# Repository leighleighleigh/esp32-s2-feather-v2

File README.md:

# leighs-featherwings
Various feathers and featherwings of my own design. 
This repo currently in a state of disarray and abandonment.

I designed an [Adafruit Feather](https://learn.adafruit.com/adafruit-feather/feather-specification) form factor board based around an ESP32-S2 microcontroller module, driven out of the need for a suitable devboard for some of my projects. 

Featherwings for power+CAN, bluetooth audio, and I2S audio output, were also designed to accompany the ESP32-S2 feather. These were all intended to be used together, in various car-related projects.

The BM83 bluetooth audio featherwing was successful when used with a [UDA1334 DAC](https://learn.adafruit.com/adafruit-i2s-stereo-decoder-uda1334a), but it was incompatible with my own DAC featherwing due to I2S timing mis-configurations.

As many of these parts became unavailable in 2020 onward, development ceased. 
Going forward, lessons learnt from these PCBs will be applied to the [saab-93NG-bluetooth-aux](https://github.com/leighleighleigh/saab-93NG-bluetooth-aux) and [saab-93NG-HPD-hacker](https://github.com/leighleighleigh/saab-93NG-HPD-hacker) projects.

# Build Images

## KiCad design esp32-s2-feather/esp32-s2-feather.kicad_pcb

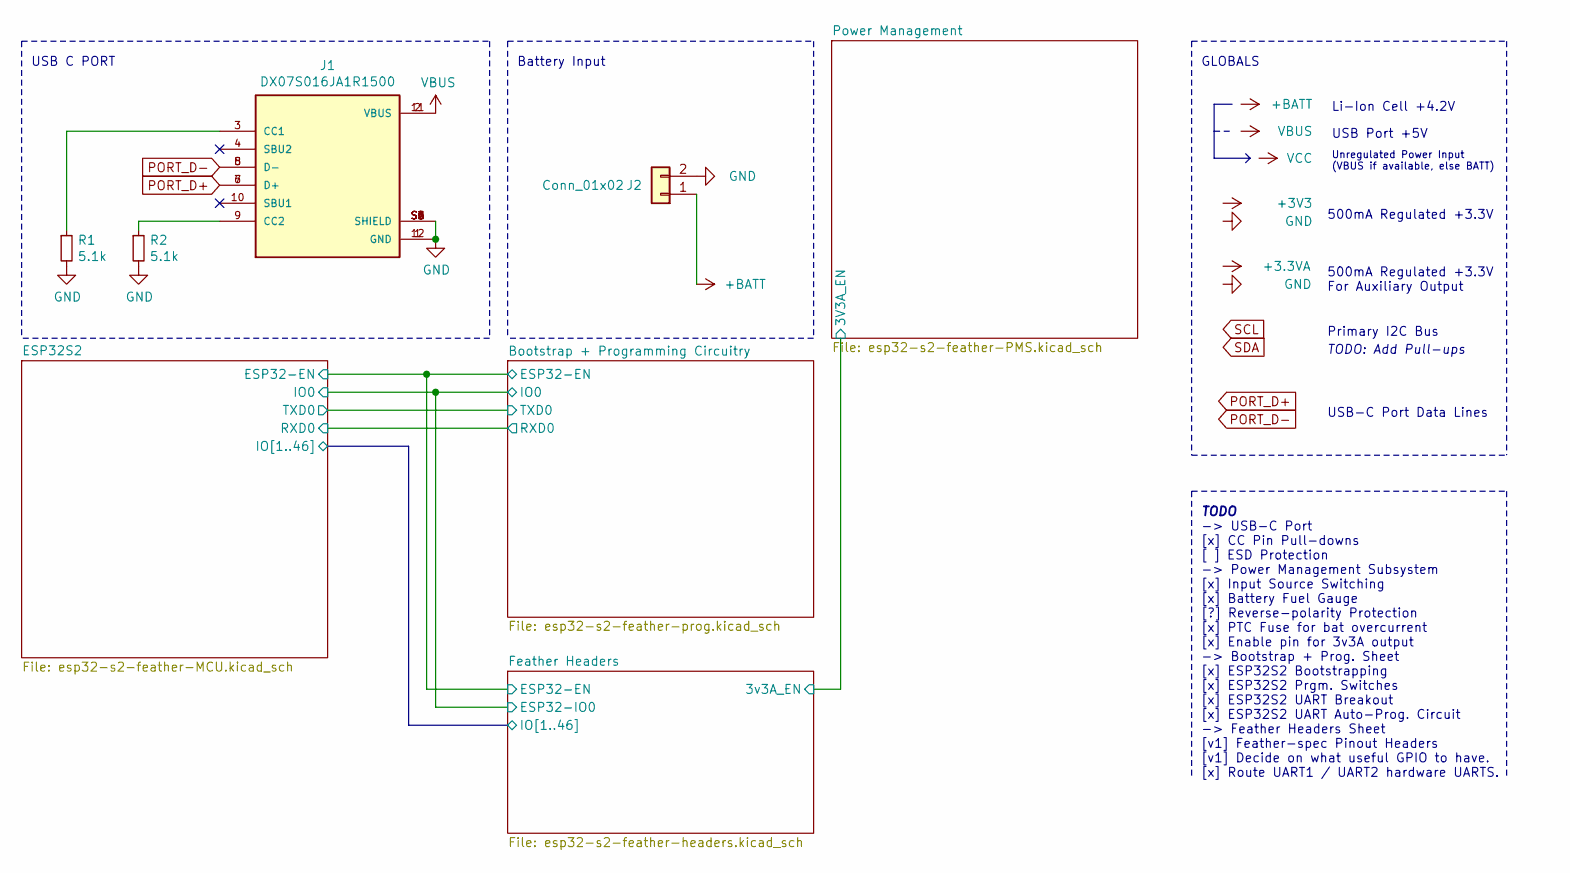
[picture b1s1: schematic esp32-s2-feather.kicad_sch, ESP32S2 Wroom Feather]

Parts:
J1: DX07S016JA1R1500; JAE_DX07S016JA1R1500; PARTREV 1
J2: Conn_01x02; JST_PH_S2B-PH-SM4-TB_1x02-1MP_P2.00mm_Horizontal
R1, R2: 5.1k; R_0805_2012Metric_Pad1.20x1.40mm_HandSolder

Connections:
+BATT: J2.1; also elsewhere on the board
GND: J1.1 (GND), J1.12 (GND), J1.S1 (SHIELD), J1.S2 (SHIELD), J1.S3 (SHIELD), J1.S4 (SHIELD), J1.S5 (SHIELD), J1.S6 (SHIELD), J2.2, R1.2, R2.2; also elsewhere on the board
unnamed: J1.3 (CC1), R1.1
unnamed: J1.9 (CC2), R2.1
PORT_D+: J1.6 (D+), J1.7 (D+); also elsewhere on the board
PORT_D-: J1.5 (D-), J1.8 (D-); also elsewhere on the board
VBUS: J1.2 (VBUS), J1.11 (VBUS); also elsewhere on the board

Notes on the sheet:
USB C PORT
Battery Input
GLOBALS
TODO
-> USB-C Port [x] CC Pin Pull-downs [ ] ESD Protection -> Power Management Subsystem [x] Input Source Switching [x] Battery Fuel Gauge [?] Reverse-polarity Protection [x] PTC Fuse for bat overcurrent [x] Enable pin for 3v3A output -> Bootstrap + Prog. Sheet [x] ESP32S2 Bootstrapping [x] ESP32S2 Prg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
500mA Regulated +3.3V
500mA Regulated +3.3V For Auxiliary Output
Primary I2C Bus
TODO: Add Pull-ups
USB-C Port Data Lines
Li-Ion Cell +4.2V
USB Port +5V
Unregulated Power Input (VBUS if available, else BATT)

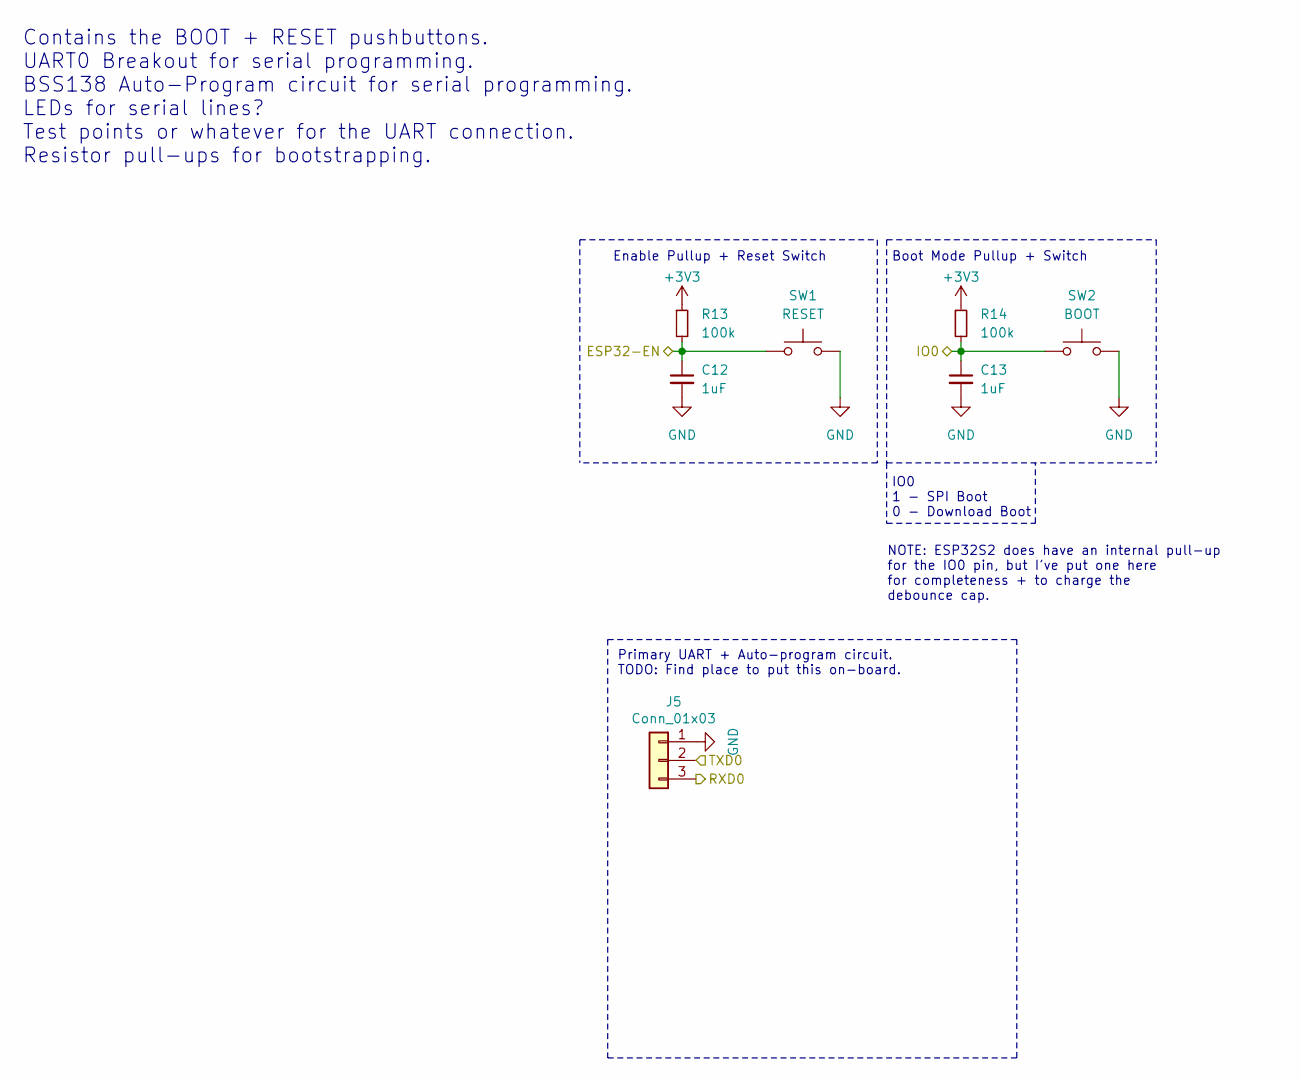
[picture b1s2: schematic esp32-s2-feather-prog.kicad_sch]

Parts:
C12, C13: 1uF; C_0805_2012Metric_Pad1.18x1.45mm_HandSolder
J5: Conn_01x03; SolderWirePad_1x03_P3.175mm_Drill0.8mm
R13, R14: 100k; R_0805_2012Metric_Pad1.20x1.40mm_HandSolder
SW1: RESET; PTS636SK25SMTRLFS
SW2: BOOT; PTS636SK25SMTRLFS

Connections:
+3V3: R13.1, R14.1; also elsewhere on the board
/ESP32-EN: C12.1, R13.2, SW1.1; also elsewhere on the board
/IO0: C13.1, R14.2, SW2.1; also elsewhere on the board
GND: C12.2, C13.2, J5.1, SW1.2, SW2.2; also elsewhere on the board

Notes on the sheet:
Contains the BOOT + RESET pushbuttons. UART0 Breakout for serial programming. BSS138 Auto-Program circuit for serial programming. LEDs for serial lines? Test points or whatever for the UART connection. Resistor pull-ups for bootstrapping.
Enable Pullup + Reset Switch
Primary UART + Auto-program circuit. TODO: Find place to put this on-board.
NOTE: ESP32S2 does have an internal pull-up for the IO0 pin, but I've put one here for completeness + to charge the debounce cap.
Boot Mode Pullup + Switch
IO0 1 - SPI Boot 0 - Download Boot

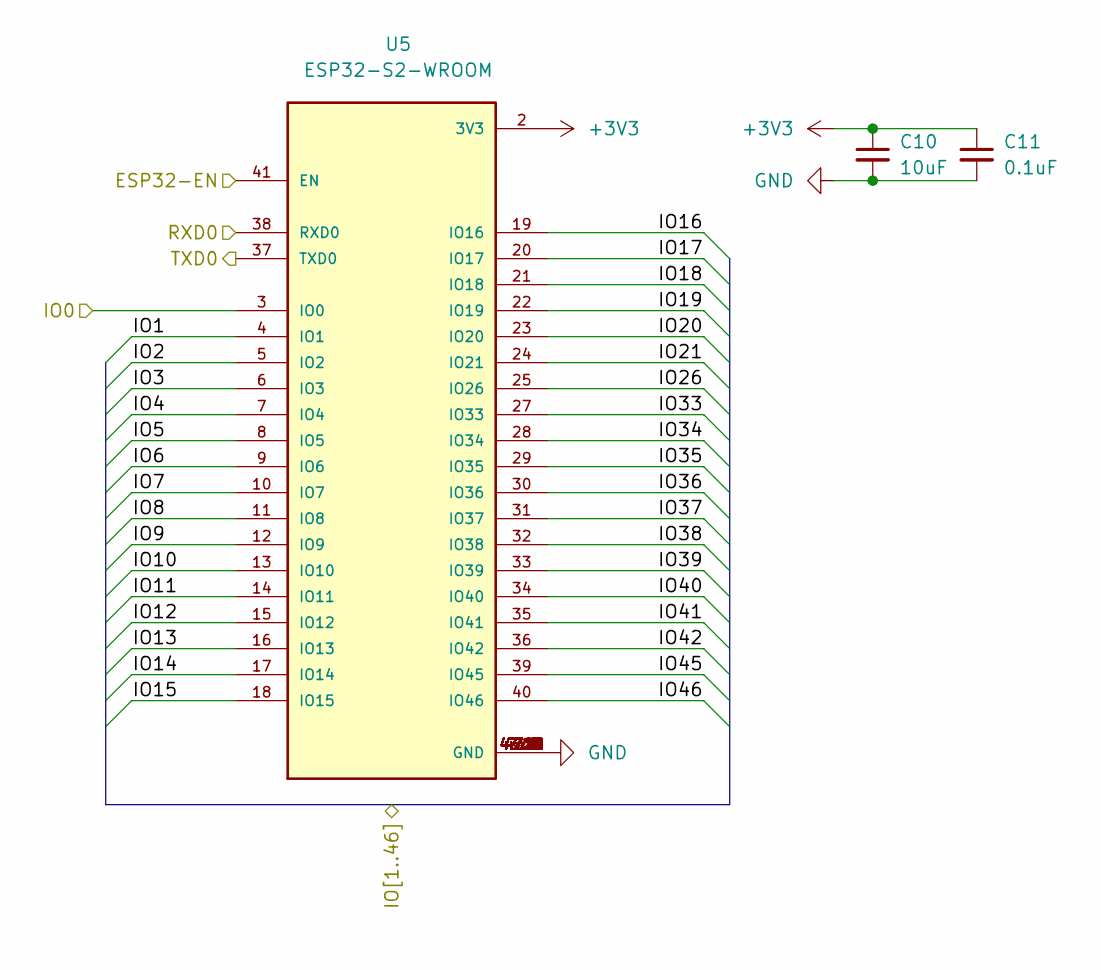
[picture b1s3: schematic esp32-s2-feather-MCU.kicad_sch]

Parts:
C10: 10uF; C_0805_2012Metric_Pad1.18x1.45mm_HandSolder
C11: 0.1uF; C_0805_2012Metric_Pad1.18x1.45mm_HandSolder
U5: ESP32-S2-WROOM; XCVR_ESP32-S2-WROOM-TinyPads; PARTREV V1.0

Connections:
+3V3: C10.1, C11.1, U5.2 (3V3); also elsewhere on the board
/ESP32-EN: U5.41 (EN); also elsewhere on the board
/IO0: U5.3 (IO0); also elsewhere on the board
/IO1: U5.4 (IO1); also elsewhere on the board
/IO2: U5.5 (IO2); also elsewhere on the board
/IO3: U5.6 (IO3); also elsewhere on the board
/IO4: U5.7 (IO4); also elsewhere on the board
/IO5: U5.8 (IO5); also elsewhere on the board
/IO6: U5.9 (IO6); also elsewhere on the board
/IO7: U5.10 (IO7); also elsewhere on the board
/IO10: U5.13 (IO10)
/IO11: U5.14 (IO11)
/IO12: U5.15 (IO12); also elsewhere on the board
/IO13: U5.16 (IO13)
/IO14: U5.17 (IO14); also elsewhere on the board
/IO15: U5.18 (IO15)
/IO16: U5.19 (IO16)
/IO17: U5.20 (IO17); also elsewhere on the board
/IO18: U5.21 (IO18); also elsewhere on the board
/IO21: U5.24 (IO21); also elsewhere on the board
/IO26: U5.25 (IO26); also elsewhere on the board
/IO33: U5.27 (IO33); also elsewhere on the board
/IO34: U5.28 (IO34); also elsewhere on the board
/IO35: U5.29 (IO35); also elsewhere on the board
/IO36: U5.30 (IO36); also elsewhere on the board
/IO37: U5.31 (IO37); also elsewhere on the board
/IO38: U5.32 (IO38)
/IO39: U5.33 (IO39)
/IO40: U5.34 (IO40)
/IO41: U5.35 (IO41)
/IO42: U5.36 (IO42)
/IO45: U5.39 (IO45)
/IO46: U5.40 (IO46)
/RXD0: U5.38 (RXD0); also elsewhere on the board
/TXD0: U5.37 (TXD0); also elsewhere on the board
GND: C10.2, C11.2, U5.1 (GND), U5.26 (GND), U5.42 (GND), U5.43.1 (GND), U5.43.2 (GND), U5.43.3 (GND), U5.43.4 (GND), U5.43.5 (GND), U5.43.6 (GND), U5.43.7 (GND), U5.43.8 (GND), U5.43.9 (GND), U5.43.10 (GND), U5.43.11 (GND), U5.43.12 (GND), U5.43.13 (GND), U5.43.14 (GND), U5.43.15 (GND), U5.43.16 (GND), U5.43.17 (GND), U5.43.18 (GND), U5.43.19 (GND), U5.43.20 (GND), U5.43.21 (GND); also elsewhere on the board
PORT_D+: U5.23 (IO20); also elsewhere on the board
PORT_D-: U5.22 (IO19); also elsewhere on the board
SCL: U5.12 (IO9); also elsewhere on the board
SDA: U5.11 (IO8); also elsewhere on the board

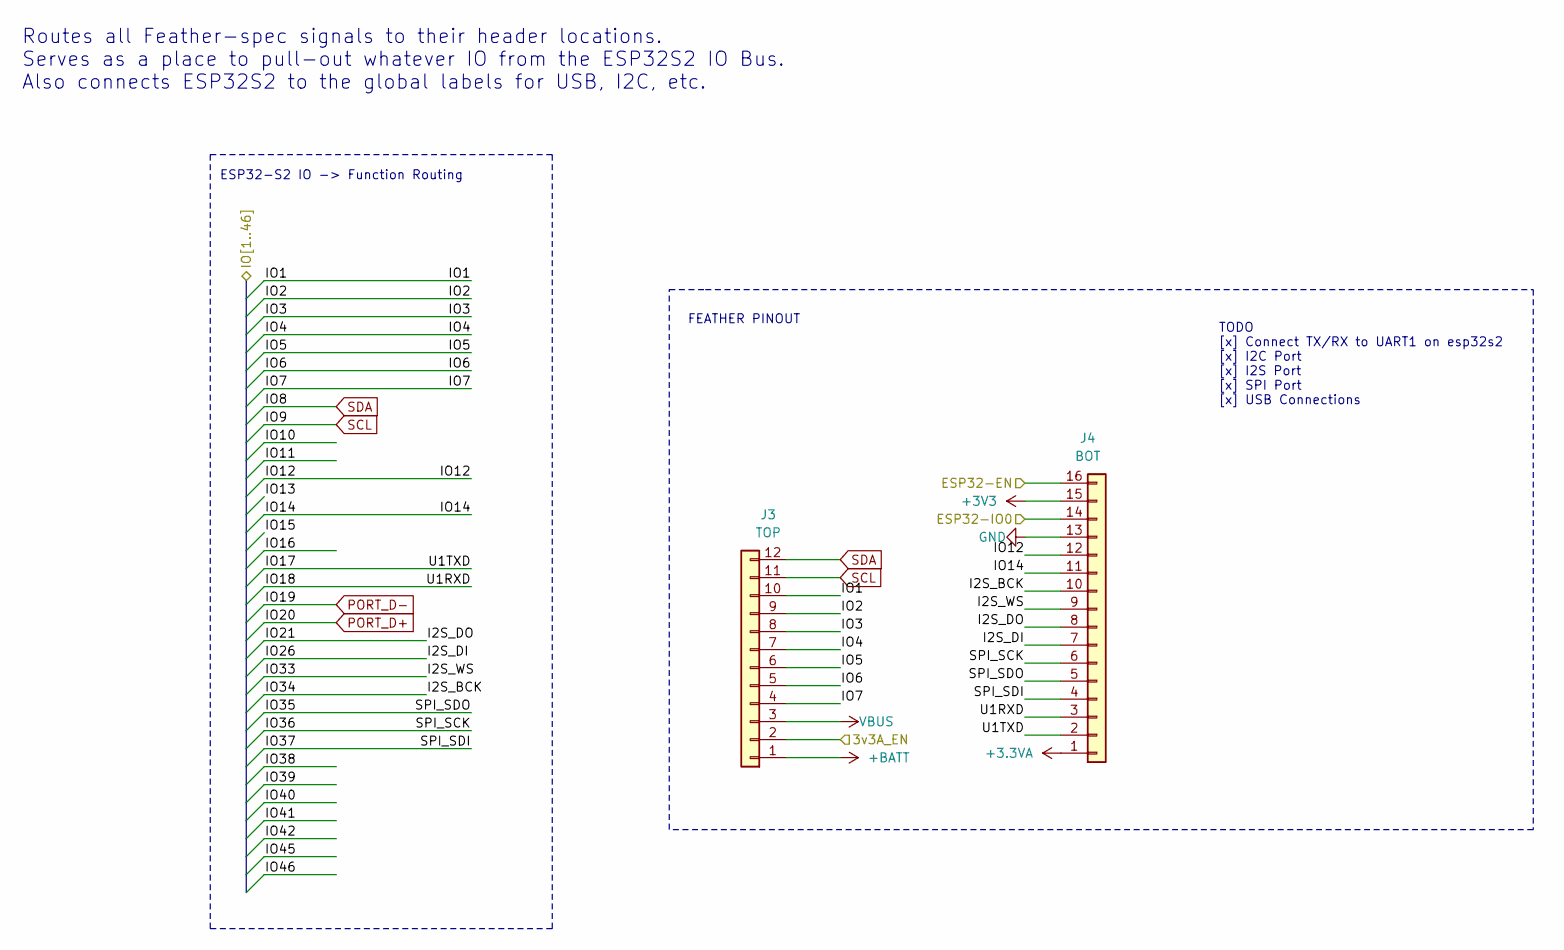
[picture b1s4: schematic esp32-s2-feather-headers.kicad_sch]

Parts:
J3: TOP; RoundPinHeader_1x12
J4: BOT; RoundPinHeader_1x16

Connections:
+3.3VA: J4.1; also elsewhere on the board
+3V3: J4.15; also elsewhere on the board
+BATT: J3.1; also elsewhere on the board
/3V3A_EN: J3.2; also elsewhere on the board
/ESP32-EN: J4.16; also elsewhere on the board
/IO0: J4.14; also elsewhere on the board
/IO1: J3.10; also elsewhere on the board
/IO2: J3.9; also elsewhere on the board
/IO3: J3.8; also elsewhere on the board
/IO4: J3.7; also elsewhere on the board
/IO5: J3.6; also elsewhere on the board
/IO6: J3.5; also elsewhere on the board
/IO7: J3.4; also elsewhere on the board
/IO12: J4.12; also elsewhere on the board
/IO14: J4.11; also elsewhere on the board
/IO17: J4.2; also elsewhere on the board
/IO18: J4.3; also elsewhere on the board
/IO21: J4.8; also elsewhere on the board
/IO26: J4.7; also elsewhere on the board
/IO33: J4.9; also elsewhere on the board
/IO34: J4.10; also elsewhere on the board
/IO35: J4.5; also elsewhere on the board
/IO36: J4.6; also elsewhere on the board
/IO37: J4.4; also elsewhere on the board
GND: J4.13; also elsewhere on the board
SCL: J3.11; also elsewhere on the board
SDA: J3.12; also elsewhere on the board
VBUS: J3.3; also elsewhere on the board

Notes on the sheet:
Routes all Feather-spec signals to their header locations. Serves as a place to pull-out whatever IO from the ESP32S2 IO Bus. Also connects ESP32S2 to the global labels for USB, I2C, etc.
ESP32-S2 IO -> Function Routing
FEATHER PINOUT
TODO [x] Connect TX/RX to UART1 on esp32s2 [x] I2C Port [x] I2S Port [x] SPI Port [x] USB Connections

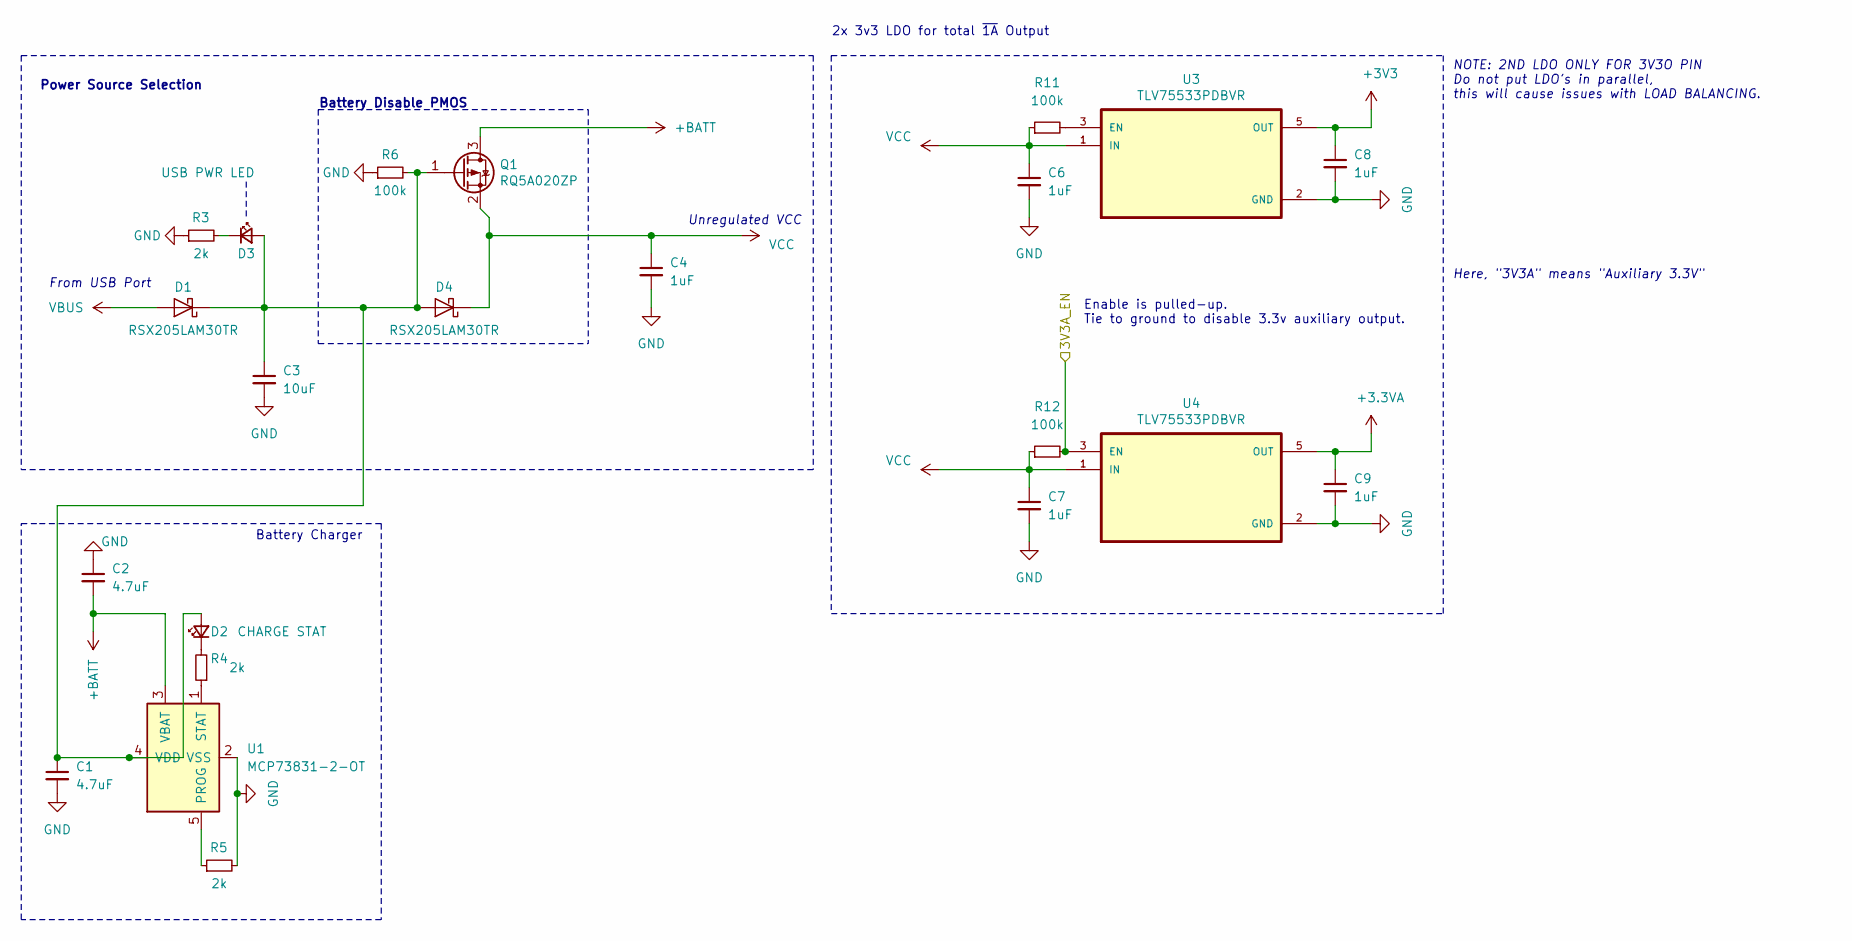
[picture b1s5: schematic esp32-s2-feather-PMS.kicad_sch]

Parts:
C1, C2: 4.7uF; C_0805_2012Metric_Pad1.18x1.45mm_HandSolder
C3: 10uF; C_0805_2012Metric_Pad1.18x1.45mm_HandSolder
C4, C6, C7, C8, C9: 1uF; C_0805_2012Metric_Pad1.18x1.45mm_HandSolder
D1, D4: RSX205LAM30TR; D_SOD-128
D2: CHARGE STAT; LED_0805_2012Metric_Pad1.15x1.40mm_HandSolder
D3: USB PWR LED; LED_0805_2012Metric_Pad1.15x1.40mm_HandSolder
Q1: RQ5A020ZP; SOT346
R3, R4, R5: 2k; R_0805_2012Metric_Pad1.20x1.40mm_HandSolder
R6, R11, R12: 100k; R_0805_2012Metric_Pad1.20x1.40mm_HandSolder
U1: MCP73831-2-OT; SOT-23-5
U3, U4: TLV75533PDBVR; SOT95P280X145-5N

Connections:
+3.3VA: C9.1, U4.5 (OUT); also elsewhere on the board
+3V3: C8.1, U3.5 (OUT); also elsewhere on the board
+BATT: C2.2, Q1.3 (D), U1.3 (VBAT); also elsewhere on the board
/3V3A_EN: R12.2, U4.3 (EN); also elsewhere on the board
GND: C1.2, C2.1, C3.2, C4.2, C6.2, C7.2, C8.2, C9.2, R3.1, R5.2, R6.1, U1.2 (VSS), U3.2 (GND), U4.2 (GND); also elsewhere on the board
unnamed: C1.1, C3.1, D1.1 (K), D2.2 (A), D3.2 (A), D4.2 (A), Q1.1 (G), R6.2, U1.4 (VDD)
unnamed: D2.1 (K), R4.2
unnamed: D3.1 (K), R3.2
unnamed: R4.1, U1.1 (STAT)
unnamed: R5.1, U1.5 (PROG)
unnamed: R11.2, U3.3 (EN)
VBUS: D1.2 (A); also elsewhere on the board
VCC: C4.1, C6.1, C7.1, D4.1 (K), Q1.2 (S), R11.1, R12.1, U3.1 (IN), U4.1 (IN)

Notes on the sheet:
Power Source Selection
From USB Port
Battery Disable PMOS
Battery Charger
Unregulated VCC
2x 3v3 LDO for total ~1A Output
Enable is pulled-up. Tie to ground to disable 3.3v auxiliary output.
NOTE: 2ND LDO ONLY FOR 3V3O PIN Do not put LDO's in parallel, this will cause issues with LOAD BALANCING.
Here, "3V3A" means "Auxiliary 3.3V"

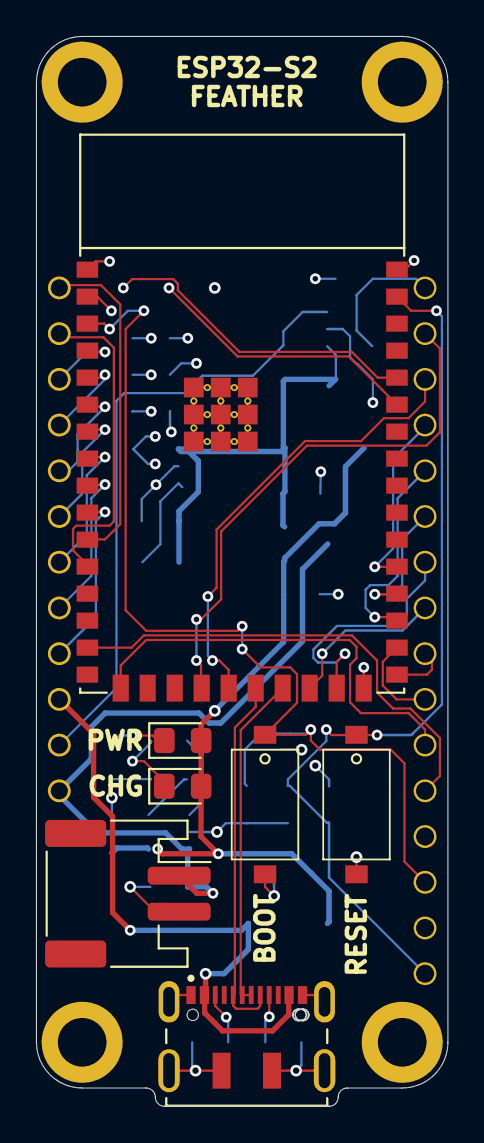
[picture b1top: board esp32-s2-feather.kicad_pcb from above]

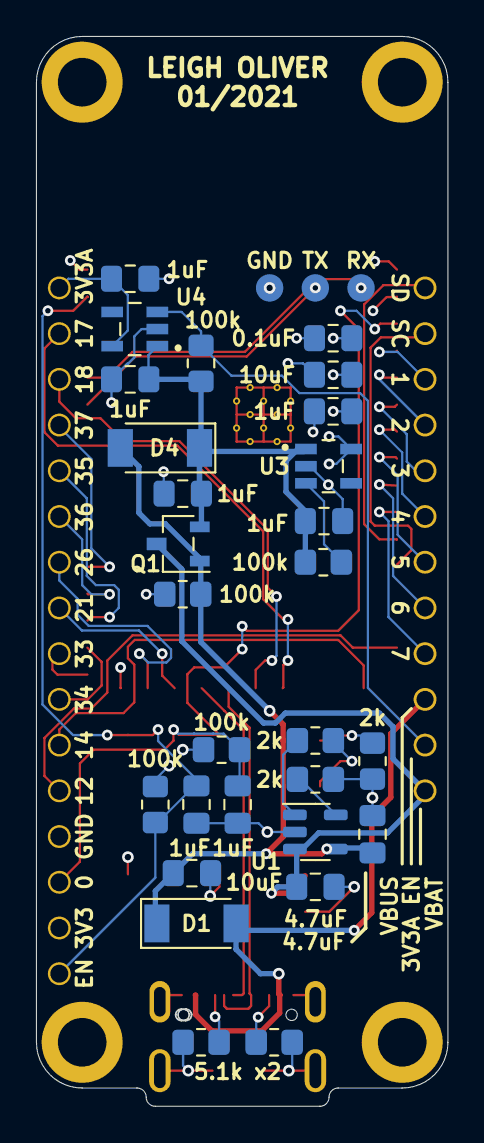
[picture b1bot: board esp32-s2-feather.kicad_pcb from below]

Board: 4 copper layers, 22.8 x 59.4 mm, 38 parts (29 on the bottom side), 41 nets.

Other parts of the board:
GND: Conn_01x03; SolderWirePad_1x03_P3.175mm_Drill0.8mm

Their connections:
/RXD0: GND.3; also elsewhere on the board
/TXD0: GND.2; also elsewhere on the board
GND: GND.1; also elsewhere on the board

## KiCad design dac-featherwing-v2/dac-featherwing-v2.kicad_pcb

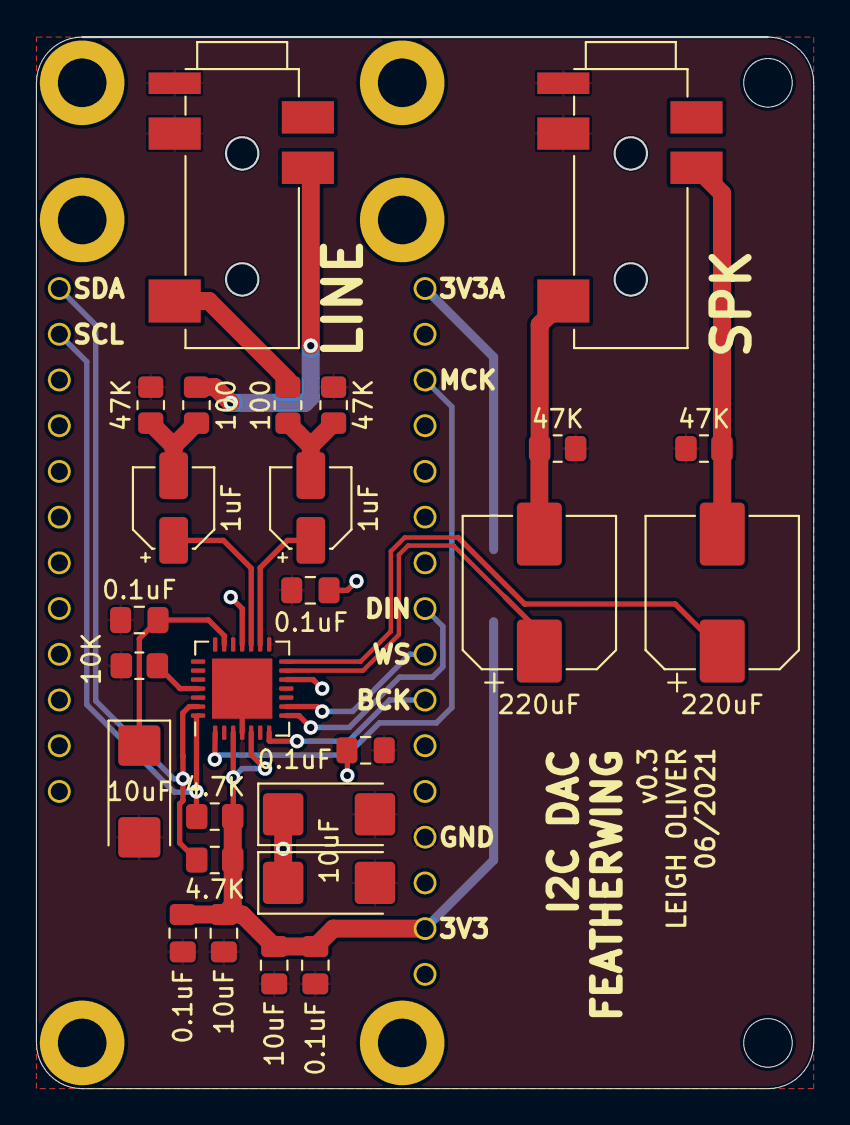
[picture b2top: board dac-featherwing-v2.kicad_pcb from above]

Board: 2 copper layers, 43.1 x 58.4 mm, 29 parts (1 on the bottom side), 22 nets.

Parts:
3V3A SRC: 3V3A SRC; SolderJumper-3_P2.0mm_Open_TrianglePad1.0x1.5mm_NumberLabels
C1, C4, C5, C8, C9: 0.1uF; C_0805_2012Metric_Pad1.18x1.45mm_HandSolder
C2, C3: 10uF; C_0805_2012Metric_Pad1.18x1.45mm_HandSolder
C6, C7, C14: 10uF; CP_EIA-6032-20_AVX-F_Pad2.25x2.35mm_HandSolder
C10, C12: 1uF; CP_Elec_4x4.5
C11, C13: 220uF; CP_Elec_8x10
J1: BOT; RoundPinHeader_1x16
J2: TOP; RoundPinHeader_1x12
J3: SPK; Lumberg 1503 20 VP3
J4: LINE; Lumberg 1503 20 VP3
R1, R2: 4.7K; R_0805_2012Metric_Pad1.20x1.40mm_HandSolder
R3: 10K; R_0805_2012Metric_Pad1.20x1.40mm_HandSolder
R5, R6, R7, R8: 47K; R_0805_2012Metric_Pad1.20x1.40mm_HandSolder
R9, R10: 100; R_0805_2012Metric_Pad1.20x1.40mm_HandSolder
U1: WM8731CLSEFL; QFN-28-1EP_5x5mm_P0.5mm_EP3.35x3.35mm

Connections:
+3.3VA: 3V3A SRC.2 (C), C5.1, C6.1, C7.1, C8.1, U1.12 (HPVDD), U1.18 (AVDD)
+3.3VDAC: 3V3A SRC.3 (B), J1.1
+3V3: 3V3A SRC.1 (A), C1.1, C2.1, C3.1, C4.1, J1.15, R1.1, R2.2, U1.3 (DCVDD), U1.5 (DBVDD)
/I2S_BCK: J1.10, U1.7 (BCLK)
/I2S_DO: J1.8, U1.8 (DACDAT)
/I2S_MCLK: J1.3, U1.1 (XTI/MCLK)
/I2S_WS: J1.9, U1.9 (DACLRC)
GND: C1.2, C2.2, C3.2, C4.2, C5.2, C6.2, C7.2, C8.2, C9.2, C14.2, J1.13, J3.R2, J3.S, J4.R2, J4.S, R3.2, R5.1, R6.2, R7.1, R8.2, U1.4 (DGND), U1.15 (HPGND), U1.19 (AGND), U1.26 (~CSB), U1.29 (AGND)
LHPOUT: C11.2, J3.T, R5.2
LOUT: J4.T, R10.2
unnamed: C10.1, U1.17 (ROUT)
unnamed: C10.2, R7.2, R9.1
unnamed: C11.1, U1.13 (LHPOUT)
unnamed: C12.1, U1.16 (LOUT)
unnamed: C12.2, R8.1, R10.1
unnamed: C13.1, U1.14 (RHPOUT)
unnamed: C9.1, C14.1, U1.20 (VMID)
unnamed: R3.1, U1.25 (MODE)
RHPOUT: C13.2, J3.R1, R6.1
ROUT: J4.R1, R9.2
SCL: J2.11, R2.1, U1.28 (SCLK)
SDA: J2.12, R1.2, U1.27 (SDIN)

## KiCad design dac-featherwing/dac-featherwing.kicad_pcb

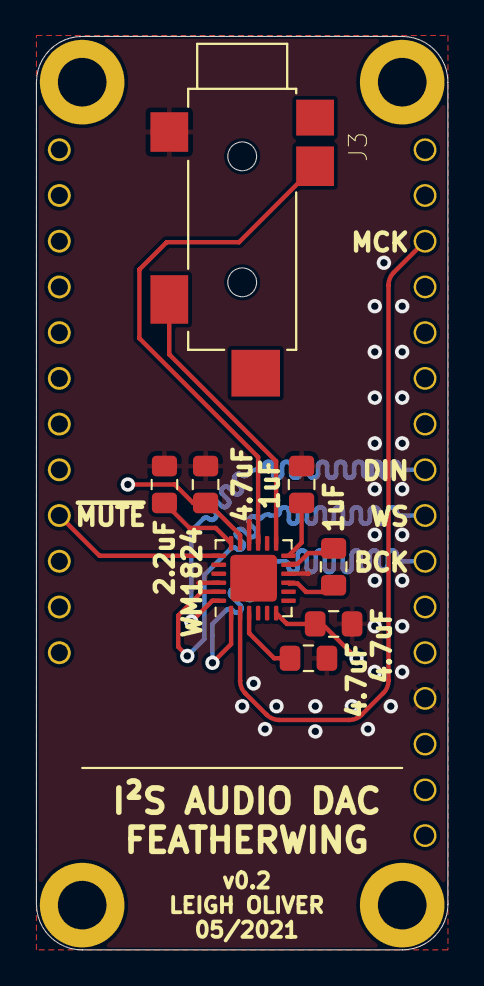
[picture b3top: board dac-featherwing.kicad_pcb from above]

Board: 2 copper layers, 22.9 x 50.7 mm, 10 parts (0 on the bottom side), 13 nets.

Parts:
C1, C2, C5: 4.7uF; C_0805_2012Metric_Pad1.15x1.40mm_HandSolder
C3, C4: 1uF; C_0805_2012Metric_Pad1.15x1.40mm_HandSolder
C6: 2.2uF; C_0805_2012Metric_Pad1.15x1.40mm_HandSolder
J1: BOT; RoundPinHeader_1x16
J2: TOP; RoundPinHeader_1x12
J3: 35RASMT4BHNTRX; SWITCHCRAFT_35RASMT4BHNTRX
U1: WM1824; QFN-24-1EP_4x4mm_P0.5mm_EP2.6x2.6mm

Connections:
+3V3: C2.1, C5.1, J1.15, U1.6 (LINEVDD), U1.17 (AVDD)
/I2S_BCK: J1.10, U1.1 (BCLK)
/I2S_DO: J1.8, U1.24 (DACDAT)
/I2S_WS: J1.9, U1.23 (LRCLK)
/OUTL: J3.2, U1.15 (LINEVOUTL)
/OUTR: J3.3, U1.13 (LINEVOUTR)
/~MUTE: J2.4, U1.19 (~MUTE)
GND: C1.2, C2.2, C4.2, C5.2, C6.2, J1.13, J3.1, U1.10 (LINEGND), U1.16 (AGND), U1.22 (AIFMODE)
unnamed: C1.1, U1.3 (DBVDD)
unnamed: C3.1, U1.9 (CPCA)
unnamed: C3.2, U1.11 (CPCB)
unnamed: C4.1, U1.12 (CPVOUTN)
unnamed: C6.1, U1.18 (VMID)

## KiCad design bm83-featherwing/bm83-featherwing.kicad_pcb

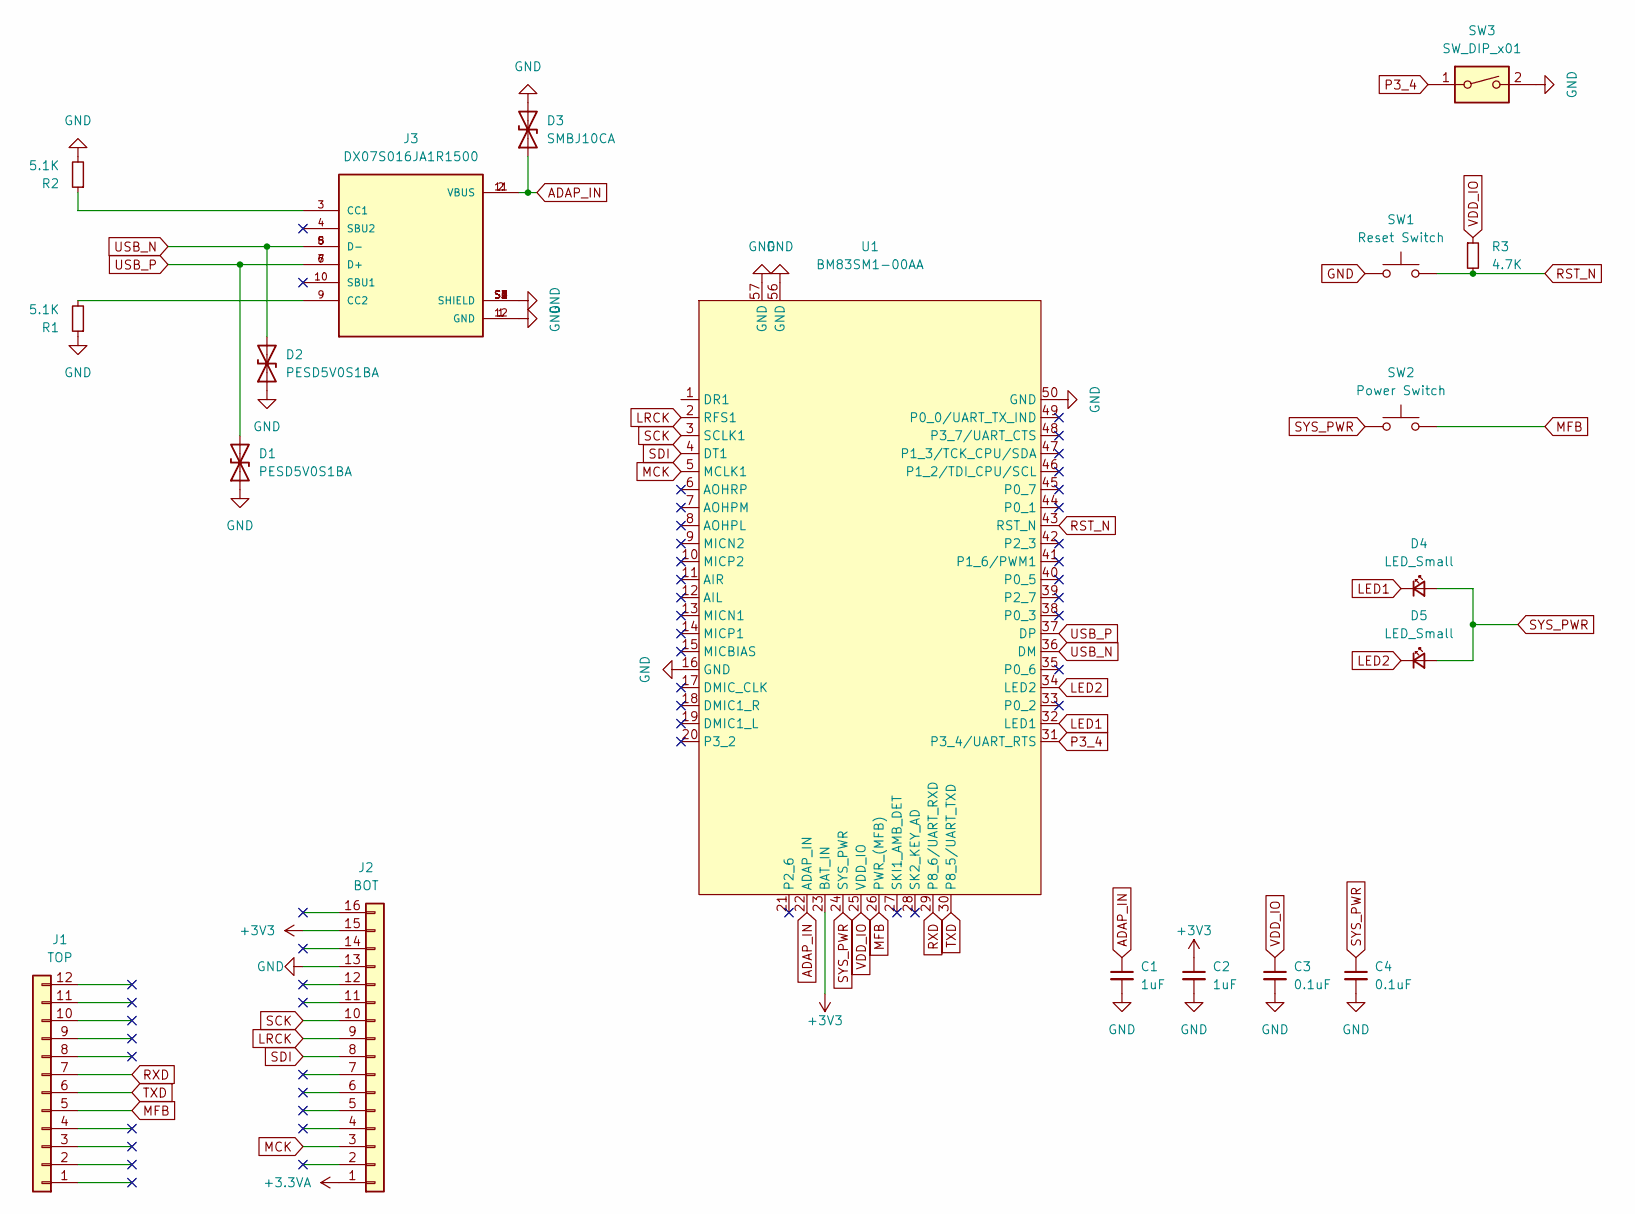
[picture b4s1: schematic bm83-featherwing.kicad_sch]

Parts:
C1, C2: 1uF; C_0805_2012Metric_Pad1.18x1.45mm_HandSolder
C3, C4: 0.1uF; C_0805_2012Metric_Pad1.18x1.45mm_HandSolder
D1, D2: PESD5V0S1BA; D_SOD-323_HandSoldering
D3: SMBJ10CA; D_SMB_Handsoldering
D4, D5: LED_Small; LED_0805_2012Metric_Pad1.15x1.40mm_HandSolder
J1: TOP; RoundPinHeader_1x12
J2: BOT; RoundPinHeader_1x16
J3: DX07S016JA1R1500; JAE_DX07S016JA1R1500; PARTREV 1
R1, R2: 5.1K; R_0805_2012Metric_Pad1.20x1.40mm_HandSolder
R3: 4.7K; R_0805_2012Metric_Pad1.20x1.40mm_HandSolder
SW1: Reset Switch; PTS636SK25SMTRLFS
SW2: Power Switch; PTS636SK25SMTRLFS
SW3: SW_DIP_x01; SW_DIP_SPSTx01_Slide_Copal_CHS-01A_W5.08mm_P1.27mm_JPin
U1: BM83SM1-00AA

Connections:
+3.3VA: J2.1
+3V3: C2.1, J2.15, U1.23 (BAT_IN)
ADAP_IN: C1.1, D3.1 (A1), J3.2 (VBUS), J3.11 (VBUS), U1.22 (ADAP_IN)
GND: C1.2, C2.2, C3.2, C4.2, D1.1 (A1), D2.1 (A1), D3.2 (A2), J2.13, J3.1 (GND), J3.12 (GND), J3.S1 (SHIELD), J3.S2 (SHIELD), J3.S3 (SHIELD), J3.S4 (SHIELD), J3.S5 (SHIELD), J3.S6 (SHIELD), R1.1, R2.2, SW1.1, SW3.2, U1.16 (GND), U1.50 (GND), U1.56 (GND), U1.57 (GND)
LED1: D4.1 (K), U1.32 (LED1)
LED2: D5.1 (K), U1.34 (LED2)
LRCK: J2.9, U1.2 (RFS1)
MCK: J2.3, U1.5 (MCLK1)
MFB: J1.5, SW2.2, U1.26 (PWR_(MFB))
unnamed: J3.3 (CC1), R2.1
unnamed: J3.9 (CC2), R1.2
P3_4: SW3.1, U1.31 (P3_4/UART_RTS)
RST_N: R3.2, SW1.2, U1.43 (RST_N)
RXD: J1.7, U1.29 (P8_6/UART_RXD)
SCK: J2.10, U1.3 (SCLK1)
SDI: J2.8, U1.4 (DT1)
SYS_PWR: C4.1, D4.2 (A), D5.2 (A), SW2.1, U1.24 (SYS_PWR)
TXD: J1.6, U1.30 (P8_5/UART_TXD)
USB_N: D2.2 (A2), J3.5 (D-), J3.8 (D-), U1.36 (DM)
USB_P: D1.2 (A2), J3.6 (D+), J3.7 (D+), U1.37 (DP)
VDD_IO: C3.1, R3.1, U1.25 (VDD_IO)

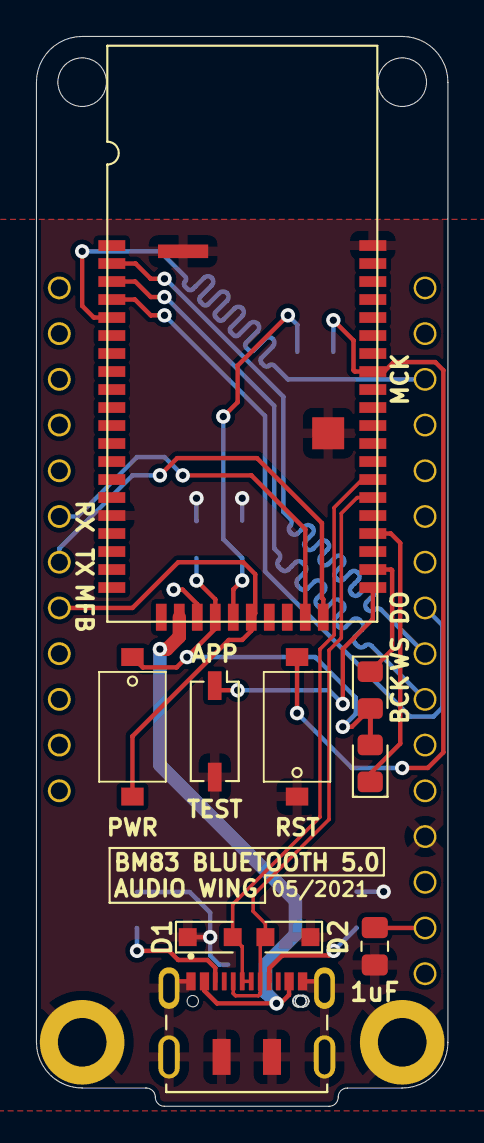
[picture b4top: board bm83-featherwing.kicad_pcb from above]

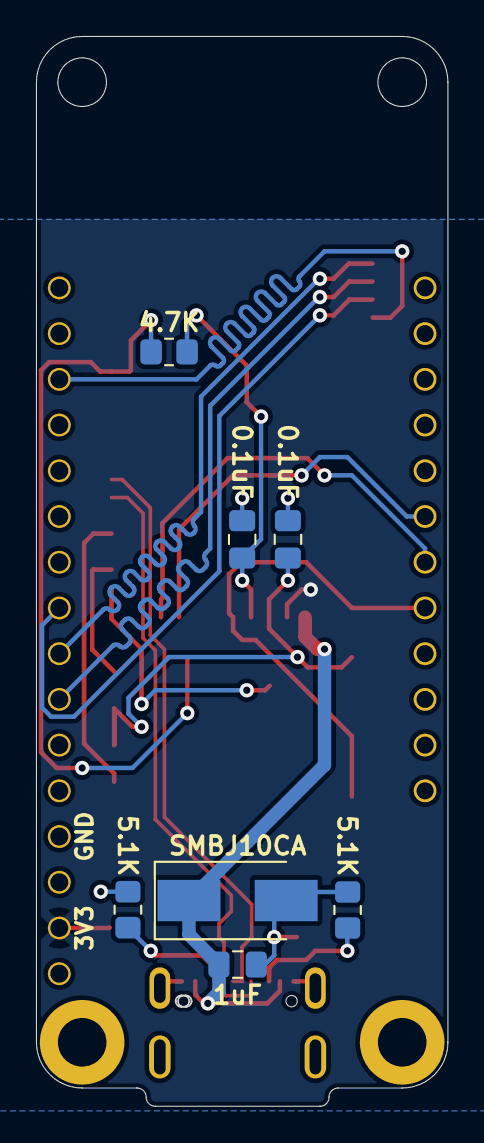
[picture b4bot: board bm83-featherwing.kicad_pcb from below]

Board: 2 copper layers, 22.8 x 59.4 mm, 19 parts (7 on the bottom side), 20 nets.

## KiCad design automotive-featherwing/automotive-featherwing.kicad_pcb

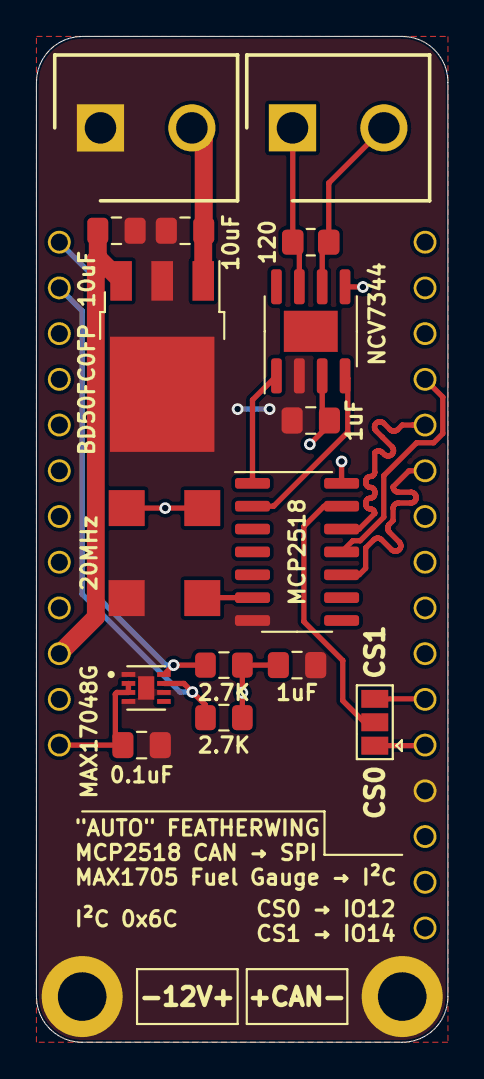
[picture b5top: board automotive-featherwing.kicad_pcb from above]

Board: 2 copper layers, 22.9 x 55.9 mm, 18 parts (0 on the bottom side), 18 nets.

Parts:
C1: 0.1uF; C_0805_2012Metric_Pad1.18x1.45mm_HandSolder
C2, C3: 10uF; C_0805_2012Metric_Pad1.18x1.45mm_HandSolder
C4, C5: 1uF; C_0805_2012Metric_Pad1.18x1.45mm_HandSolder
CAN0: Conn_01x02; Phoenix_1985865
IC1: BD50FC0FP; TO-252-3_TabPin2
IC2: NCV7344; SOIC-8-1EP_3.9x4.9mm_P1.27mm_EP2.29x3mm
J1: Conn_01x12; RoundPinHeader_1x12
J2: CAN; RoundPinHeader_1x16
J3: Conn_01x02; Phoenix_1985865
JP1: CS0; SolderJumper-3_P1.3mm_Open_Pad1.0x1.5mm
R1: 120; R_0805_2012Metric_Pad1.20x1.40mm_HandSolder
R2, R3: 2.7K; R_0805_2012Metric_Pad1.15x1.40mm_HandSolder
U1: MAX17048G; SON50P200X200X80-9N
U2: MCP2518; SOIC-14_3.9x8.7mm_P1.27mm
X2: 20MHz; Oscillator_SMD_EuroQuartz_XO91-4Pin_7.0x5.0mm

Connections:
+3V3: C4.1, C5.1, IC2.3 (VCC), IC2.5 (NC_(-0)_VIO_(-3)), J2.1, R2.2, R3.2, U2.14 (VDD), X2.1 (EN), X2.4 (V+)
+5V: C3.1, IC1.3 (VO), J1.3
+BATT: C1.2, J1.1, U1.2 (CELL), U1.3 (VDD)
CS: JP1.2 (C), U2.13 (NCS)
GND: C1.1, C2.2, C3.2, C4.2, C5.2, IC1.2 (GND), IC2.2 (GND), J2.13, J3.1, U1.1 (CTG), U1.4 (GND), U1.6 (QSTRT), U1.9 (EP), U2.7 (VSS), X2.2 (GND)
unnamed: CAN0.1, IC2.7 (CANH), R1.1
unnamed: CAN0.2, IC2.6 (CANL), R1.2
unnamed: IC2.1 (TXD), U2.1 (TXCAN)
unnamed: IC2.4 (RXD), U2.2 (RXCAN)
SCK: J2.6, U2.10 (SCK)
SDA: J1.12, R3.1, U1.8 (SDA)
SDI: J2.4, U2.11 (SDI)
SDL: J1.11, R2.1, U1.7 (SCL)
SDO: J2.5, U2.12 (SDO)
SYSCLK: U2.6 (OSC1), X2.3 (OUT)
VCC: C2.1, IC1.1 (VCC), J3.2
~CS0: J2.12, JP1.1 (A)
~CS1: J2.11, JP1.3 (B)
